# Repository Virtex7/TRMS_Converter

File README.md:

TRMS_Converter
==============

echter True-RMS-Wandler für Stromwandler.

Der Wandler wurde für die Verwendung von 10mA-Drehspulinstrumenten an einem Stromwandler gebaut, damit diese Anzeigen, die bekanntlich den arithmetischen Mittelwert und nicht den geometrischen Mittelwert anzeigen. Der TRMS-Wandler benötigt eine 9-15VDC-Spannungsversorgung und kann bis zu 1V_RMS als Eingabesignal verarbeiten und gibt eine bis ca 20mA belastbare, trimmbare Spannung aus, an die die Anzeige oder der ADC-Pin direkt angeschlossen werden kann.

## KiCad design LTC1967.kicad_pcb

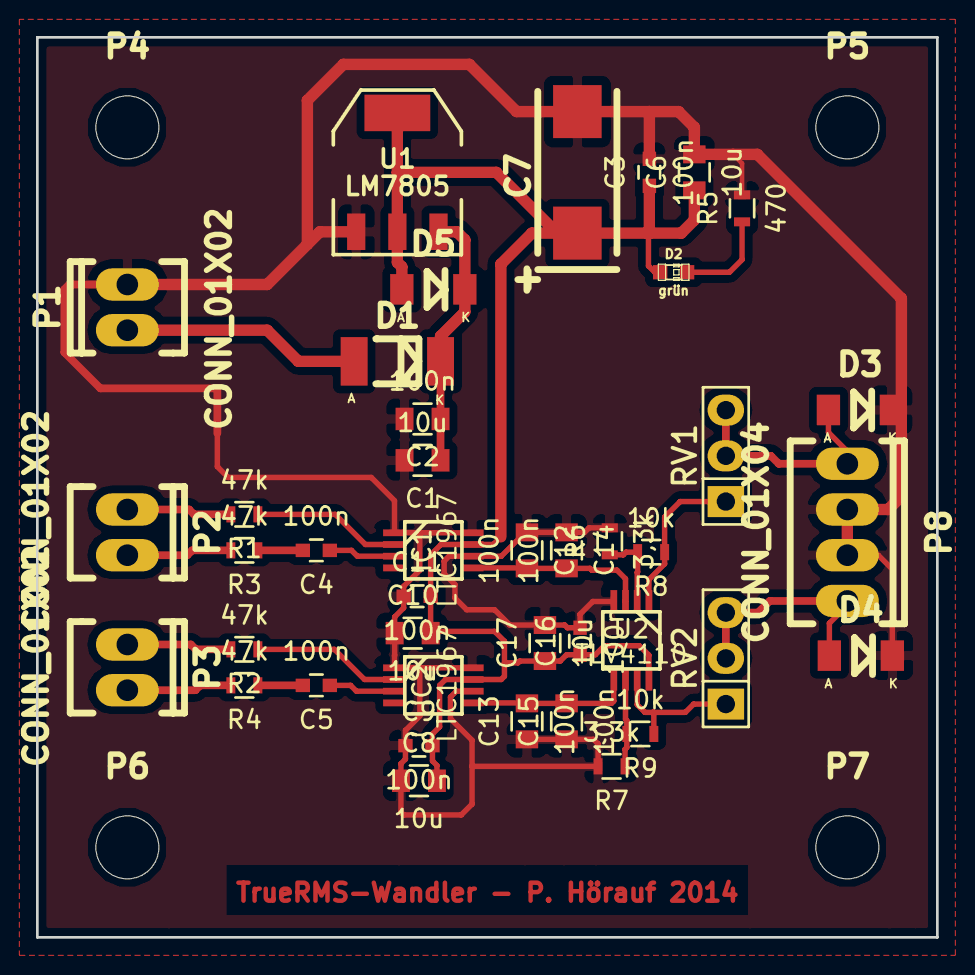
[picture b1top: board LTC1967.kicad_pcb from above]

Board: 2 copper layers, 50.0 x 50.0 mm, 45 parts (0 on the bottom side), 23 nets.

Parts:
C1, C6, C8, C10, C17: 10u; C_0805
C2, C12, C13, C14, C15: 100n; C_0805
C3, C4, C5, C9, C11, C16: 100n; C_0603
C7: 47u; TantalC_SizeD_EIA-7343_Wave
D1: 1n4001; Diode-MELF_Standard
D2: grün; LED-0603
D3, D4, D5: 1n4148; Diode-MiniMELF_Standard
IC1, IC2: LTC1967; MSOP-8
P1, P2, P3: CONN_01X02; Socket_MOLEX-KK-RM2-54mm_Lock_2pin_straight
P4, P5, P6, P7: CONN_01X01; MountingHole_3-5mm
P8: CONN_01X04; Socket_MOLEX-KK-RM2-54mm_Lock_4pin_straight
R1, R2, R3, R4: 47k; R_0603
R5: 470; R_0603
R6, R7: 3,3k; R_0603
R8, R9: 10k; R_0603
RV1, RV2: 500; Pin_Header_Straight_1x03
U1: LM7805; SOT-223
U2: TLV4110; MSOP-8

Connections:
+5V: C3.1, C6.1, C7.1, C8.2, C9.2, C10.2, C11.2, C16.1, C17.1, D2.1, D5.1, IC1.7, IC2.7, U1.VO, U2.8
GND: C1.2, C2.2, C3.2, C6.2, C7.2, C8.1, C9.1, C10.1, C11.1, C12.1, C13.1, C14.1, C15.1, C16.2, C17.2, D3.2, D4.2, IC1.1, IC1.6, IC1.8, IC2.1, IC2.6, IC2.8, P1.2, P8.2, P8.3, R5.2, R6.2, R7.2, U1.GND, U2.4
unnamed: C1.1, C2.1, D1.2, D5.2, U1.VI
unnamed: C4.1, IC1.3
unnamed: C4.2, R3.1
unnamed: C5.1, IC2.3
unnamed: C5.2, R4.1
unnamed: C12.2, C14.2, IC1.5, U2.3
unnamed: C13.2, C15.2, IC2.5, U2.5
unnamed: D1.1, P1.1
unnamed: D2.2, R5.1
unnamed: D3.1, P8.1, RV1.2, RV1.3
unnamed: D4.1, P8.4, RV2.2, RV2.3
unnamed: IC1.2, R1.1
unnamed: IC2.2, R2.1
unnamed: P2.1, R1.2
unnamed: P2.2, R3.2
unnamed: P3.1, R2.2
unnamed: P3.2, R4.2
unnamed: R6.1, R8.2, U2.2
unnamed: R7.1, R9.2, U2.6
unnamed: R8.1, RV1.1, U2.1
unnamed: R9.1, RV2.1, U2.7

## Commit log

2014-11-13 init
2014-11-13 readme mit etwas content gefüllt
